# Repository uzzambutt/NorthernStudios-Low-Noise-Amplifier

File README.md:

# NorthernStudios Wideband VHF/UHF Low-Noise Amplifier

<p align="center">
  <b>Designed by: Muhammad Uzzam Butt // NorthernStudios</b>
</p>

<p align="center">

</p>

---

## Overview

The **NorthernStudios Wideband VHF/UHF Low-Noise Amplifier (LNA)** is an open-source, high-linearity RF preamplifier designed for weak-signal reception across the VHF and UHF bands. Built around the Qorvo / RFMD SPF5189Z GaAs pHEMT MMIC, it operates as an unfiltered wideband gain block with active drain biasing, multi-stage supply rail decoupling, and dedicated input ESD protection.

The board is tailored for satellite telemetry decoding (such as 137 MHz NOAA APT / Meteor-M LRPT and 435-438 MHz CubeSats), amateur radio communications on the 2m (144-148 MHz) and 70cm (430-440 MHz) bands, and general-purpose wideband Software Defined Radio (SDR) receiver front-ends.

The RF signal paths use 50-ohm single-ended coplanar waveguide (CPW) geometry with continuous via fences to maintain impedance matching and minimize parasitic coupling with the power regulation circuitry.

---

## Hardware Specifications

### RF & Electrical Performance

| Parameter | Specification | Notes |
| :--- | :--- | :--- |
| **Optimized Tuning Band** | 130 MHz - 450 MHz | Weather satellite and VHF/UHF amateur radio spectrum |
| **Operational Bandwidth** | 50 MHz - 4000 MHz | Unfiltered MMIC frequency range |
| **VHF Gain** | ~18.5 dB | Measured at 144 MHz |
| **UHF Gain** | ~18.0 dB | Measured at 435 MHz |
| **Noise Figure (NF)** | ~0.60 dB | Typical across VHF and UHF bands |
| **Port Impedance** | 50 ohm nominal | Matched RF input (J1) and output (J2) |
| **Input ESD Tolerance** | +/- 30 kV air / +/- 30 kV contact | IEC 61000-4-2 standard via onboard low-capacitance clamp |

### Linearity by Operating Mode

| Metric | High-Dynamic-Range Mode (5.0V Bias) | Safe Thermal Mode (3.3V Bias) |
| :--- | :--- | :--- |
| **Drain Voltage (V_D)** | +5.0 V DC | ~3.3 V DC |
| **Current Consumption** | ~90 - 95 mA | ~80 mA |
| **Device Dissipation** | ~450 mW | ~264 mW |
| **Output P1dB** | +22.7 dBm | ~ +18 dBm |
| **Output IP3 (OIP3)** | +39.5 dBm | ~ +34 dBm |
| **Configuration** | Install two 0-ohm jumpers at R1 and R2 | Install two 39-ohm resistors in parallel at R1 and R2 |

---

## Circuit Architecture

### RF Signal Path
* **DC Blocking**: 1 nF (1000 pF) 0603 C0G/NP0 ceramic capacitors (C3 and C4) isolate the input and output RF ports while presenting minimal series reactance (Xc ~ 1.1 ohm at 144 MHz, ~ 0.37 ohm at 435 MHz).
* **Active Bias Choke**: High-Q wirewound ceramic-core inductor (L1, 470 nH to 1.0 uH) injects DC drain current at MMIC Pin 3 with a self-resonant frequency (SRF) exceeding 500 MHz to prevent in-band signal leakage.
* **ESD Clamping**: Nexperia PESD5V0U1BL bidirectional ESD clamp diode (D3, SOD-882) located at the input port shunts high-voltage transients up to +/- 30 kV. Its ultra-low diode capacitance (Cd ~ 1.5 pF) maintains input match and avoids degrading noise figure.

### Power Regulation & Protection
* **DC Input (J3)**: Accepts +7.0 V to +10.0 V DC via screw terminal block or standard 0.1-inch (2.54 mm) pin header.
* **Linear LDO**: AMS1117-5.0 (U2) in a SOT-223 package steps down input supply to a clean, ripple-free +5.0 V DC rail.
* **Reverse Polarity Protection**: Series SS34 Schottky barrier diode (D1) on the positive rail prevents reverse-current damage. A secondary shunt SS34 diode (D2) clamps reverse spikes at the input terminal.
* **Multi-Decade Decoupling Ladder**: A combination of bulk 22 uF polarized tantalum capacitors (C1, C2) and parallel ceramic bypass capacitors (C7: 100 nF X7R, C6: 10 nF X7R, C5: 100 pF C0G) isolates the active device from power supply noise across low, intermediate, and high RF frequencies.

### Selectable Thermal / Linearity Biasing
The board features a dual parallel 0805 resistor footprint (R1 || R2) between the 5V LDO output and the RF bias choke:
* **High-Dynamic-Range Mode**: Solder two 0-ohm jumpers in place of R1 and R2. The MMIC runs directly at 5.0 V / 90 mA for maximum linearity (+39.5 dBm OIP3), suitable for high-interference environments with adequate thermal dissipation.
* **Safe Thermal Mode**: Solder two 39-ohm resistors in parallel (19.5 ohm net resistance). This drops the drain voltage to ~3.3 V and reduces active MMIC power dissipation from 450 mW to 264 mW, lowering operating temperatures significantly when operating without active cooling.

---

## Critical Components (Bill of Materials)

| Reference | Value / Part | Footprint | Function / Description |
| :--- | :--- | :--- | :--- |
| **U1** | SPF5189Z | SOT-89-3 | High-linearity GaAs pHEMT low-noise MMIC amplifier |
| **U2** | AMS1117-5.0 | SOT-223-3 | +5.0V fixed linear low-dropout voltage regulator |
| **D1, D2** | SS34 | DO-214AC (SMA) | 3A / 40V Schottky barrier diodes (series protection D1, shunt clamp D2) |
| **D3** | PESD5V0U1BL | SOD-882 | Ultra-low capacitance (1.5 pF) bidirectional ESD clamp diode |
| **C1, C2** | 22 uF / 16V | EIA-3528-21 (Case-B) | Polarized tantalum capacitors for DC bulk input and output filtering |
| **C3, C4** | 1 nF (1000 pF) | 0603 | C0G / NP0 dielectric RF DC blocking capacitors |
| **C5** | 100 pF | 0603 | C0G dielectric RF high-frequency decoupling capacitor |
| **C6** | 10 nF | 0603 | X7R dielectric intermediate frequency bypass capacitor |
| **C7** | 100 nF | 0603 | X7R dielectric low-frequency bypass capacitor |
| **L1** | 470 nH - 1.0 uH | 0805 | Wirewound ceramic-core RF bias inductor (SRF > 500 MHz) |
| **R1, R2** | 39 ohm or 0 ohm | 0805 | Parallel bias ballast resistors (39 ohm for thermal mode, 0 ohm for HDR mode) |
| **J1, J2** | 50-ohm SMA Female | End-Launch Edge Mount | RF input (J1) and RF output (J2) edge-mount coaxial connectors |
| **J3** | DC Power Input | 5.08 mm / 2.54 mm | 2-pin screw terminal block or pin header (7-10V DC input) |

---

## PCB Layout Details

* **RF Transmission Lines**: 50-ohm single-ended coplanar waveguide (CPW) calculated for standard 1.6 mm FR-4 dielectric thickness with ground stitching vias on both sides of the trace.
* **Shielding Via Fence**: Close-pitch ground via fencing surrounds the RF trace runs to suppress parasitic substrate resonances and minimize crosstalk with the DC regulation section.
* **Thermal Relief**: A 4-via thermal array is integrated directly inside the SOT-89 center ground slug pad, sinking heat into internal and bottom ground planes.
* **RF Connectors**: Edge-mount end-launch SMA female connectors soldered directly to the 50-ohm input and output CPW transmission lines.

---

## Assembly Notes

* **Reflow Requirements**: The SOD-882 package for ESD protection diode D3 has bottom-only contact pads and requires solder paste with hot-air reflow or a hot plate for proper soldering.
* **Hand Soldering**: All remaining SMD parts (0603 passives, 0805 components, SOT-89, SOT-223, DO-214AC, Case-B tantalum capacitors, and SMA connectors) include extended solder pads for manual assembly with a fine-tip soldering iron.
* **Flux Cleaning**: Residual rosin or active flux along the RF path (C3, D3, U1, C4, and L1) will increase insertion loss and degrade the noise figure. Clean the board thoroughly with isopropyl alcohol (IPA) after soldering.

---

## Repository Structure

* [`LNA/`](LNA): KiCad design files
  * [`LNA.kicad_pro`](LNA/LNA.kicad_pro): KiCad project configuration
  * [`LNA.kicad_sch`](LNA/LNA.kicad_sch): Schematic sheet
  * [`LNA.kicad_pcb`](LNA/LNA.kicad_pcb): PCB layout and routing
* [`Pic.png`](Pic.png): 3D board render preview
* [`Schematic.pdf`](Schematic.pdf): Complete schematic in PDF format

---

## License

This project is licensed under the [MIT License](LICENSE).

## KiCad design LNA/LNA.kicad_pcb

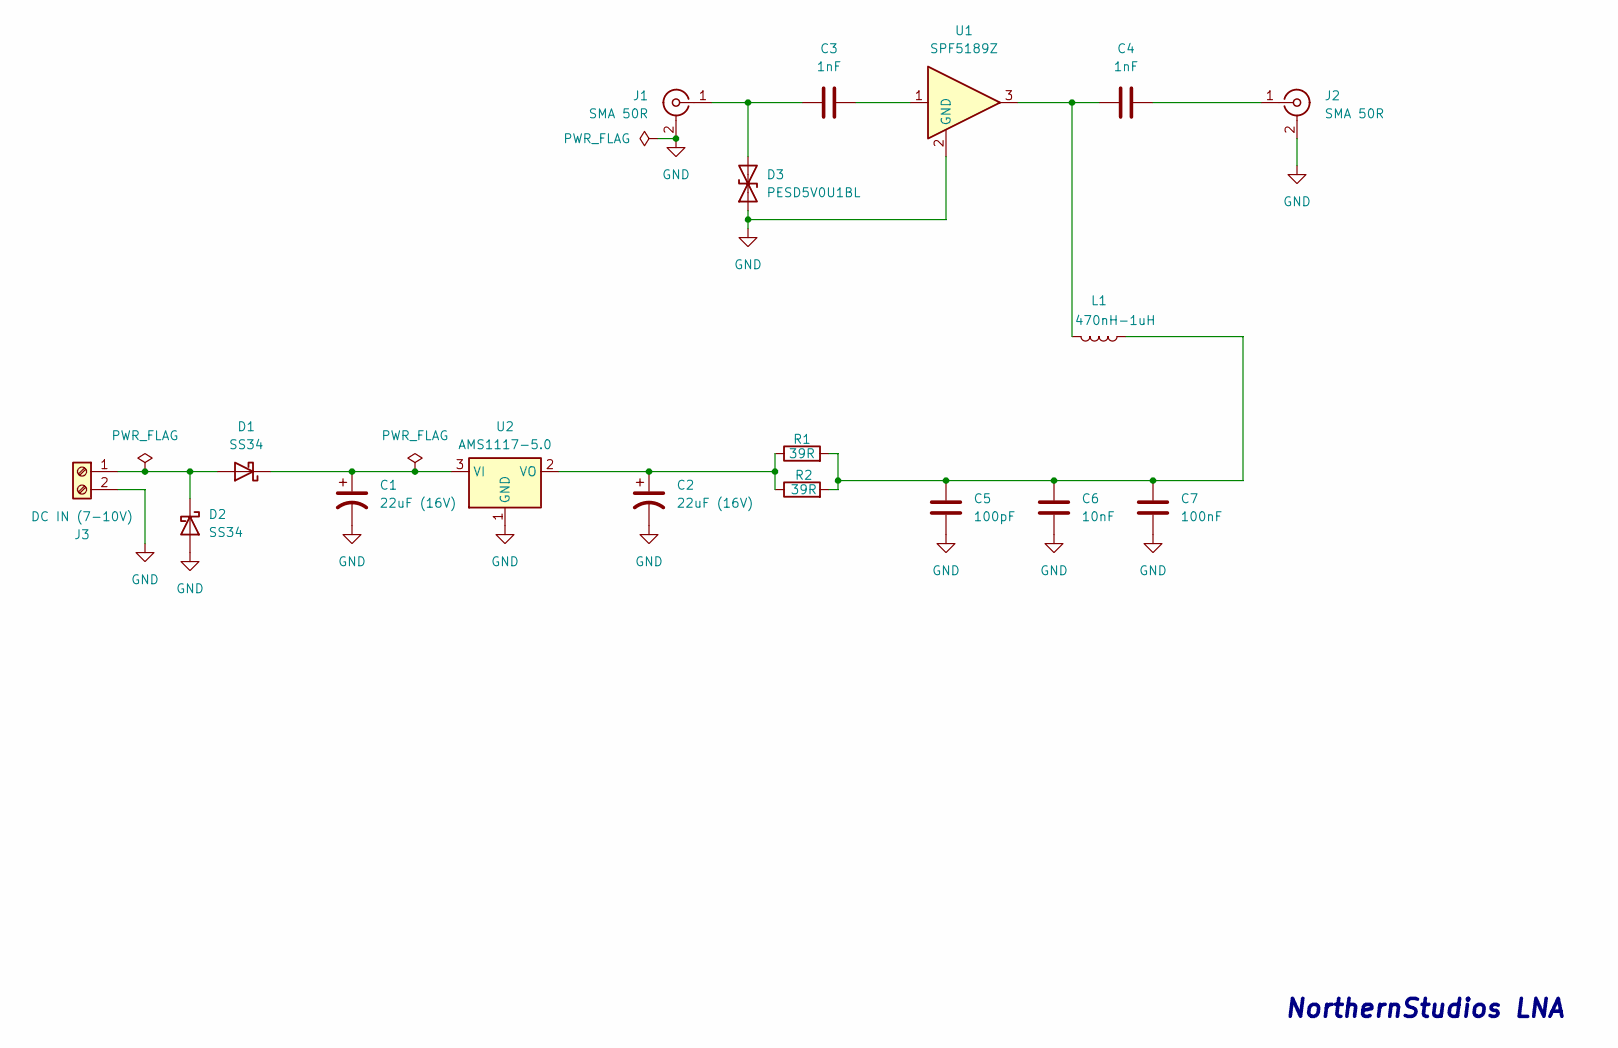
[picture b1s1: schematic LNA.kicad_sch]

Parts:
C1, C2: 22uF (16V); CP_EIA-3528-21_Kemet-B_HandSolder
C3, C4: 1nF; C_0603_1608Metric_Pad1.08x0.95mm_HandSolder
C5: 100pF; C_0603_1608Metric_Pad1.08x0.95mm_HandSolder
C6: 10nF; C_0603_1608Metric_Pad1.08x0.95mm_HandSolder
C7: 100nF; C_0603_1608Metric_Pad1.08x0.95mm_HandSolder
D1, D2: SS34; D_SMA_Handsoldering
D3: PESD5V0U1BL; D_SOD-882
J1, J2: SMA 50R; SMA_Amphenol_132289_EdgeMount
J3: DC IN (7-10V); TerminalBlock_MaiXu_MX126-5.0-02P_1x02_P5.00mm
L1: 470nH-1uH; L_0805_2012Metric
R1, R2: 39R; R_0805_2012Metric_Pad1.20x1.40mm_HandSolder
U1: SPF5189Z; SOT-89-3_Handsoldering
U2: AMS1117-5.0; SOT-223-3_TabPin2

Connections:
GND: C1.2, C2.2, C5.2, C6.2, C7.2, D2.2 (A), D3.1 (A1), J1.2 (Ext), J2.2 (Ext), J3.2, U1.2 (GND_2), U2.1 (GND)
unnamed: C3.2, U1.1
unnamed: C4.1, L1.2, U1.3
unnamed: C5.1, C6.1, C7.1, L1.1, R1.2, R2.2
unnamed: D1.2 (A), D2.1 (K), J3.1
unnamed: C1.1, D1.1 (K), U2.3 (VI)
unnamed: C3.1, D3.2 (A2), J1.1 (In)
unnamed: C4.2, J2.1 (In)
unnamed: C2.1, R1.1, R2.1, U2.2 (VO)

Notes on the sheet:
NorthernStudios LNA

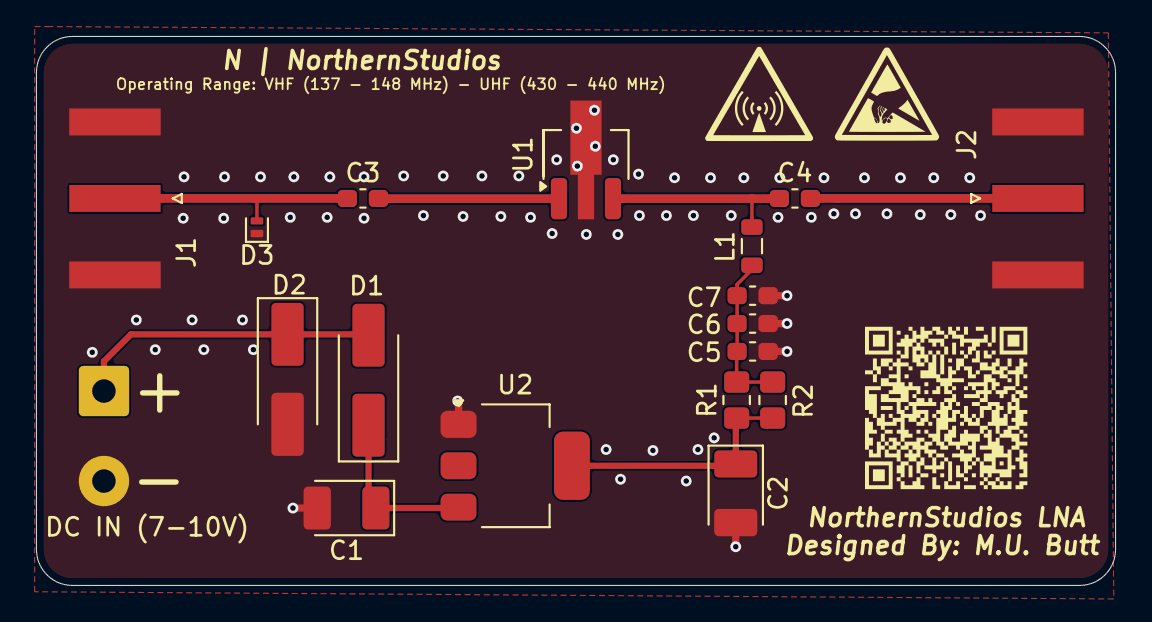
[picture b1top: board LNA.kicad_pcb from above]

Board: 4 copper layers, 59.9 x 30.5 mm, 18 parts (0 on the bottom side), 9 nets.

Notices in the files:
README.md:
License: MIT
